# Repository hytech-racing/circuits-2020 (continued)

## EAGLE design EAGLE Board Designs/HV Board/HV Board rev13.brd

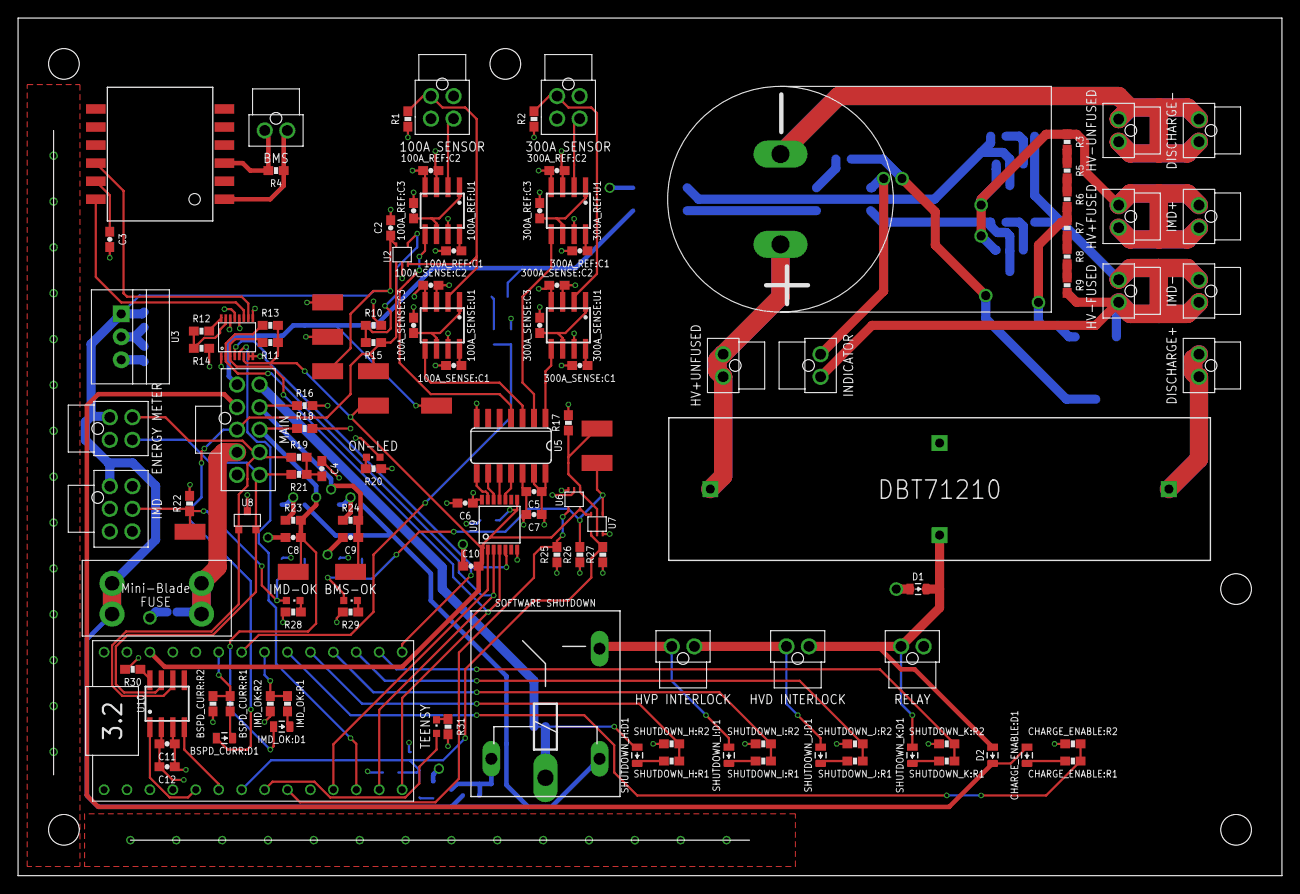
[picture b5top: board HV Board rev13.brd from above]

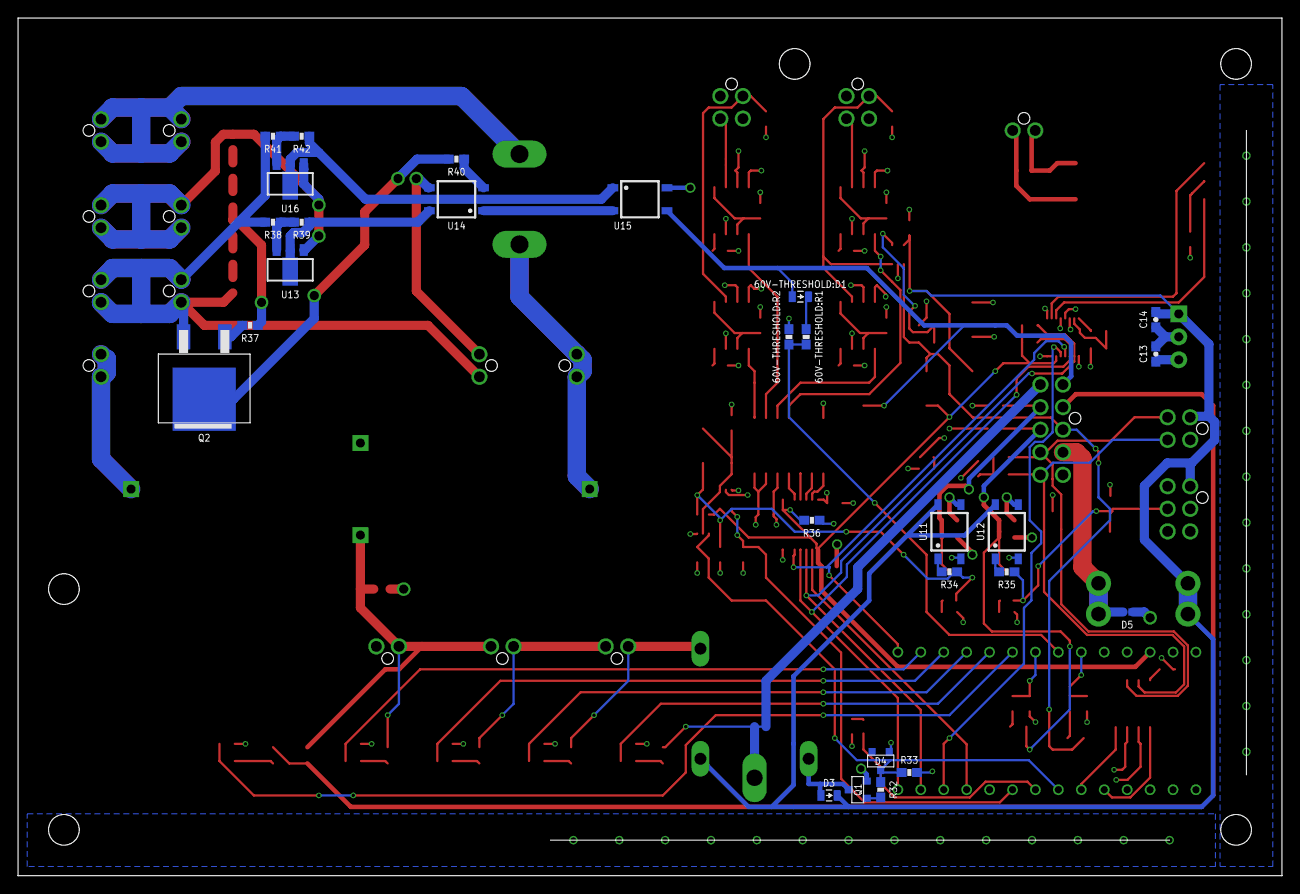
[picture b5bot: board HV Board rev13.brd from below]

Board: 4 copper layers, 140.0 x 95.0 mm, 161 parts (27 on the bottom side), 104 nets.

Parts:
60V-THRESHOLD:D1: TS4148 RYG; 0805_D
60V-THRESHOLD:R1: 12k; 0603-RES
60V-THRESHOLD:R2: 10k; 0603-RES
100A_REF:C1, 100A_SENSE:C1, 300A_REF:C1, 300A_SENSE:C1: 530pF; 0603-CAP
100A_REF:C2, 100A_REF:C3, 100A_SENSE:C2, 100A_SENSE:C3, 300A_REF:C2, 300A_REF:C3, 300A_SENSE:C2, 300A_SENSE:C3: 0.1uF; 0603-CAP
100A_REF:U1, 100A_SENSE:U1, 300A_REF:U1, 300A_SENSE:U1: MAX7480; SOIC-08
$$U$1, $$U$2: M3_MOUNTING
$$U$12: DBT71210
BMS-OK: GREEN; LED-603
BOARDFUSE: 2A; MINI-BLADE_FUSE_HOLDER
BSPD_CURR:D1: TS4148 RYG; 0805_D
BSPD_CURR:R1: 12K; 0603-RES
BSPD_CURR:R2: 43K; 0603-RES
C1: 180uF; LLS2V181MELA
C2, C5, C6, C8, C9, C10, C11: 0.1uF; 0603-CAP
C3: 27pF; 0603-CAP
C4: 4.7nF; 0603-CAP
C7, C12: 1uF; 0603-CAP
C13, C14: 10uF; 0603-CAP
CHARGE_ENABLE:D1: TS4148 RYG; 0805_D
CHARGE_ENABLE:R1: 12K; 0603-RES
CHARGE_ENABLE:R2: 43K; 0603-RES
CURRENT1: 100A SENSOR; NANO-FIT_VERTICAL-4
CURRENT2: 300A SENSOR; NANO-FIT_VERTICAL-4
D1, D2, D3: TS4148 RYG; 0805_D
D4: MMBZ5246BLT1G; SOT23
D5: TVS_DIODE; U-DFN1608-2
DISCHARGE+: DISCHARGE+; NANO-FIT_VERTICAL-2
DISCHARGE-: DISCHARGE-; NANO-FIT_VERTICAL-2
ENERGYMETER: ENERGY METER; NANO-FIT_VERTICAL-4
HV+FUSED: HV+FUSED; NANO-FIT_VERTICAL-2
HV+UNFUSED: HV+UNFUSED; NANO-FIT_VERTICAL-2
HV-FUSED: HV-FUSED; NANO-FIT_VERTICAL-2
HV-UNFUSED: HV-UNFUSED; NANO-FIT_VERTICAL-2
IMD: IMD; NANO-FIT_VERTICAL-6
IMD+: IMD+; NANO-FIT_VERTICAL-2
IMD-: IMD-; NANO-FIT_VERTICAL-2
IMD-OK: YELLOW; LED-603
IMD_OK:D1: TS4148 RYG; 0805_D
IMD_OK:R1: 12K; 0603-RES
IMD_OK:R2: 43K; 0603-RES
INDICATOR: INDICATOR; NANO-FIT_VERTICAL-2
INTERLOCK1: HVP INTERLOCK; NANO-FIT_VERTICAL-2
INTERLOCK2: HVD INTERLOCK; NANO-FIT_VERTICAL-2
ISOSPI: BMS; NANO-FIT_VERTICAL-2
MAIN: MAIN; NANO-FIT_VERTICAL-10
ON-LED: BLUE; LED-603
Q1: DMG3406L; SOT23
Q2: AOD1N60; TO-252
R1, R2, R25: 10K; 0603-RES
R3, R5, R6: 510k; 0603-RES
R4: 100; 0603-RES
R7, R8, R9: 43k; 0603-RES
R10, R12, R14, R30, R31, R40: 1k; 0603-RES
R11, R13, R39, R42: 2k; 0603-RES
R15: 1.4k; 0603-RES
R16, R17, R18, R22, R26, R27, R33, R36: 10k; 0603-RES
R19, R21: 60; 0603-RES
R20, R28, R29: 1K; 0603-RES
R23, R24: 1.6K; 0603-RES
R32, R37: 10; 0603-RES
R34: 360; 0603-RES
R35: 4.7k; 0603-RES
R38: 20k; 0603-RES
R41: 8.2k; 0603-RES
RELAY: RELAY; NANO-FIT_VERTICAL-2
SHUTDOWN_H:D1: TS4148 RYG; 0805_D
SHUTDOWN_H:R1: 12K; 0603-RES
SHUTDOWN_H:R2: 43K; 0603-RES
SHUTDOWN_I:D1: TS4148 RYG; 0805_D
SHUTDOWN_I:R1: 12K; 0603-RES
SHUTDOWN_I:R2: 43K; 0603-RES
SHUTDOWN_J:D1: TS4148 RYG; 0805_D
SHUTDOWN_J:R1: 12K; 0603-RES
SHUTDOWN_J:R2: 43K; 0603-RES
SHUTDOWN_K:D1: TS4148 RYG; 0805_D
SHUTDOWN_K:R1: 12K; 0603-RES
SHUTDOWN_K:R2: 43K; 0603-RES
SOFTWARE_SHUTDOWN: SOFTWARE SHUTDOWN; G5LE-1A4
TEENSY: RED; LED-603
TEENSY3.1: TEENSY_3.2_SIMPLE
U1: HM2102NLT
U2: OPA172; SOT323-5
U3: OKI-78SR-5; OKI-78SR
U4: LTC6820; MSOP-16
U5: MCP3204; SO14
U6: STWD100PYW83F; SOT323-5
U7: SN74LVC1G08; SOT323-5
U8: CDSOT23-T24CAN-Q; SOT23
U9: TXB0104TSSOP; TSSOP-14
U10: MCP2551; SOIC-08
U11, U12, U14, U15: CPC1002N; SOP04
U13, U16: LR8; SOT89
U$3, U$4, U$5, U$6, U$7, U$8, U$9, U$10, U$11, U$13, U$14: TEST_POINTMICRO_MINIATURE; MICRO_MINIATURE
U$15, U$16, U$17: M3_MOUNTING

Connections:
60V-THRESHOLD:INPUT_POST_DIODE: 60V-THRESHOLD:D1.C, 60V-THRESHOLD:R1.1
60V_THRESHOLD_SIGNAL: 60V-THRESHOLD:D1.A, MAIN.P$1, U15.3, U$8.P$1
60V_THRESHOLD_TEENSY: 60V-THRESHOLD:R1.2, 60V-THRESHOLD:R2.1, TEENSY3.1.A6
100A_REF: 100A_REF:U1.2, CURRENT1.P$3
100A_REF:CLK: 100A_REF:C1.1, 100A_REF:U1.8
100A_REF:COM: 100A_REF:C3.1, 100A_REF:U1.1, 100A_REF:U1.6
100A_REF_FILT: 100A_REF:U1.5, U5.4
100A_SENSE: 100A_SENSE:U1.2, CURRENT1.P$2, R1.1, U2.3
100A_SENSE:CLK: 100A_SENSE:C1.1, 100A_SENSE:U1.8
100A_SENSE:COM: 100A_SENSE:C3.1, 100A_SENSE:U1.1, 100A_SENSE:U1.6
100A_SENSE_FILT: 100A_SENSE:U1.5, U5.3
300A_REF: 300A_REF:U1.2, CURRENT2.P$3
300A_REF:CLK: 300A_REF:C1.1, 300A_REF:U1.8
300A_REF:COM: 300A_REF:C3.1, 300A_REF:U1.1, 300A_REF:U1.6
300A_REF_FILT: 300A_REF:U1.5, U5.2
300A_SENSE: 300A_SENSE:U1.2, CURRENT2.P$2, R2.1
300A_SENSE:CLK: 300A_SENSE:C1.1, 300A_SENSE:U1.8
300A_SENSE:COM: 300A_SENSE:C3.1, 300A_SENSE:U1.1, 300A_SENSE:U1.6
300A_SENSE_FILT: 300A_SENSE:U1.5, U5.1
+3V3: C10.1, R11.1, R13.1, R36.1, TEENSY3.1.3.3V, U4.6, U6.5, U7.5, U9.1, U9.8, U$7.P$1
+5V: 100A_REF:C2.1, 100A_REF:U1.4, 100A_REF:U1.7, 100A_SENSE:C2.1, 100A_SENSE:U1.4, 100A_SENSE:U1.7, 300A_REF:C2.1, 300A_REF:U1.4, 300A_REF:U1.7, 300A_SENSE:C2.1, 300A_SENSE:U1.4, 300A_SENSE:U1.7, C5.1, C6.1, C7.1, C11.2, C12.2, C13.1, CURRENT1.P$1, CURRENT2.P$1, ON-LED.A, TEENSY3.1.VIN, U3.3, U4.1, U4.7, U4.8, U4.9, U4.12, U5.13, U5.14, U9.14, U10.3, U15.4, U$4.P$1
+12V: BOARDFUSE.R1, BOARDFUSE.R2, C2.2, C14.1, D3.C, ENERGYMETER.P$1, IMD.P$1, SOFTWARE_SHUTDOWN.2, U2.5, U3.1, U11.4, U12.4, U$5.P$1
+12VIN: BOARDFUSE.L1, BOARDFUSE.L2, D5.P$2, MAIN.P$4
BMS_OK: C9.2, MAIN.P$7, R16.1, R24.2, U$14.P$1
BMS_OK_3.3V: BMS-OK.A, R26.2, R34.1, U7.4, U$10.P$1
BMS_OK_PRE_FILTER: R24.1, U11.3
BMS_STATUS: D4.3, R27.2, R32.2, R33.1, TEENSY3.1.D5, U7.1
BSPD_CURR:INPUT_POST_DIODE: BSPD_CURR:D1.C, BSPD_CURR:R1.1
BSPD_CURRENT: BSPD_CURR:D1.A, MAIN.P$3, R15.2, U2.1, U$6.P$1
BSPD_CURR_TEENSY: BSPD_CURR:R1.2, BSPD_CURR:R2.1, TEENSY3.1.A7
CANH: ENERGYMETER.P$4, MAIN.P$10, R21.2, U8.2, U10.7
CANL: ENERGYMETER.P$3, MAIN.P$9, R19.2, U8.1, U10.6
CANRX: TEENSY3.1.D4(CANRX), U10.4
CANTX: TEENSY3.1.D3(CANTX), U10.1
CHARGE_ENABLE: CHARGE_ENABLE:D1.A, D2.C, MAIN.P$2
CHARGE_ENABLE:INPUT_POST_DIODE: CHARGE_ENABLE:D1.C, CHARGE_ENABLE:R1.1
CHARGE_ENABLE_TEENSY: CHARGE_ENABLE:R1.2, CHARGE_ENABLE:R2.1, TEENSY3.1.A4
CS_ADC_5V: U5.8, U9.13
CS_ADC_TEENSY: TEENSY3.1.D9(RX2), U9.2
CS_LTC6820: TEENSY3.1.D10(TX2), U4.5
DISCHARGE+: $$U$12.CONTACT2, DISCHARGE+.P$1, DISCHARGE+.P$2
GND: 60V-THRESHOLD:R2.2, 100A_REF:C1.2, 100A_REF:C2.2, 100A_REF:C3.2, 100A_REF:U1.3, 100A_SENSE:C1.2, 100A_SENSE:C2.2, 100A_SENSE:C3.2, 100A_SENSE:U1.3, 300A_REF:C1.2, 300A_REF:C2.2, 300A_REF:C3.2, 300A_REF:U1.3, 300A_SENSE:C1.2, 300A_SENSE:C2.2, 300A_SENSE:C3.2, 300A_SENSE:U1.3, $$U$12.COIL+, BSPD_CURR:R2.2, C2.1, C3.2, C4.1, C5.2, C6.2, C7.2, C8.1, C9.1, C10.2, C11.1, C12.1, C13.2, C14.2, CHARGE_ENABLE:R2.2, CURRENT1.P$4, CURRENT2.P$4, D1.A, D4.1, D5.P$1, ENERGYMETER.P$2, IMD.P$2, IMD.P$3, IMD.P$4, IMD_OK:R2.2, MAIN.P$5, Q1.2, R1.2, R2.2, R10.2, R14.2, R16.2, R17.1, R18.2, R20.2, R22.2, R25.2, R26.1, R27.1, R28.2, R29.2, R30.1, R31.2, R33.2, R36.2, RELAY.P$2, SHUTDOWN_H:R2.2, SHUTDOWN_I:R2.2, SHUTDOWN_J:R2.2, SHUTDOWN_K:R2.2, TEENSY3.1.AGND, TEENSY3.1.GND, U2.2, U3.2, U4.13, U4.14, U5.7, U5.12, U6.2, U6.3, U7.3, U8.3, U9.7, U10.2, U11.2, U12.2, U$3.P$1
HV+FUSED: HV+FUSED.P$1, HV+FUSED.P$2, IMD+.P$1, IMD+.P$2, R3.2, U13.1, U16.1
HV+UNFUSED: $$U$12.CONTACT1, C1.P$1, HV+UNFUSED.P$1, HV+UNFUSED.P$2
HV-FUSED: HV-FUSED.P$1, HV-FUSED.P$2, IMD-.P$1, IMD-.P$2, INDICATOR.P$2, Q2.3, R9.1, R38.2, R41.2
HV-UNFUSED: C1.P$2, DISCHARGE-.P$1, DISCHARGE-.P$2, HV-UNFUSED.P$1, HV-UNFUSED.P$2
IM: U1.P$10, U4.10
IMD_OK: C8.2, IMD_OK:D1.A, MAIN.P$8, R18.1, R23.2, U$13.P$1
IMD_OK:INPUT_POST_DIODE: IMD_OK:D1.C, IMD_OK:R1.1
IMD_OK_12V: IMD.P$5, IMD-OK.A, R22.1, R35.1, U$11.P$1
IMD_OK_PRE_FILTER: R23.1, U12.3
IMD_OK_TEENSY: IMD_OK:R1.2, IMD_OK:R2.1, TEENSY3.1.A5
IP: U1.P$12, U4.11
ISOSPI-M: ISOSPI.P$2, R4.2, U1.P$3
ISOSPI-P: ISOSPI.P$1, R4.1, U1.P$1
MISO_5V: U5.10, U9.11
MISO_TEENSY: R13.2, TEENSY3.1.D12, U4.3, U9.4
MOSI_5V: U5.9, U9.12
MOSI_TEENSY: R11.2, TEENSY3.1.D11, U4.2, U9.3
unnamed: D3.A, Q1.3, SOFTWARE_SHUTDOWN.1
unnamed: ON-LED.C, R20.1
unnamed: Q2.1, R37.2
unnamed: R39.2, U13.2, U13.PAD, U14.4
unnamed: R38.1, R39.1, U13.3
unnamed: R10.1, R15.1, U2.4
unnamed: R35.2, U12.1
unnamed: IMD-OK.C, R28.1
unnamed: C4.2, R19.1, R21.1
unnamed: Q1.1, R32.1
unnamed: R34.2, U11.1
unnamed: BMS-OK.C, R29.1
unnamed: R42.2, U15.1, U16.2, U16.PAD
unnamed: R3.1, R5.1
unnamed: R5.2, R6.2
unnamed: R30.2, U10.8
unnamed: R7.1, R8.1
unnamed: R8.2, R9.2
unnamed: R31.1, TEENSY.C
unnamed: R40.1, U14.2
unnamed: R12.1, U4.16
unnamed: R12.2, R14.1, U4.15
unnamed: U14.1, U15.2
unnamed: INDICATOR.P$1, U14.3
unnamed: C3.1, U1.P$11
unnamed: R41.1, R42.1, U16.3
unnamed: R6.1, R7.2, R37.1
unnamed: Q2.2(TAB), R40.2
SCK_5V: U5.11, U9.10
SCK_TEENSY: TEENSY3.1.D13, U4.4, U9.5
SHUTDOWN_H: MAIN.P$6, SHUTDOWN_H:D1.A, SOFTWARE_SHUTDOWN.P
SHUTDOWN_H:INPUT_POST_DIODE: SHUTDOWN_H:D1.C, SHUTDOWN_H:R1.1
SHUTDOWN_H_TEENSY: SHUTDOWN_H:R1.2, SHUTDOWN_H:R2.1, TEENSY3.1.A3
SHUTDOWN_I: INTERLOCK1.P$1, SHUTDOWN_I:D1.A, SOFTWARE_SHUTDOWN.S
SHUTDOWN_I:INPUT_POST_DIODE: SHUTDOWN_I:D1.C, SHUTDOWN_I:R1.1
SHUTDOWN_I_TEENSY: SHUTDOWN_I:R1.2, SHUTDOWN_I:R2.1, TEENSY3.1.A2
SHUTDOWN_J: INTERLOCK1.P$2, INTERLOCK2.P$1, SHUTDOWN_J:D1.A
SHUTDOWN_J:INPUT_POST_DIODE: SHUTDOWN_J:D1.C, SHUTDOWN_J:R1.1
SHUTDOWN_J_TEENSY: SHUTDOWN_J:R1.2, SHUTDOWN_J:R2.1, TEENSY3.1.A1
SHUTDOWN_K: $$U$12.COIL-, D1.C, D2.A, INTERLOCK2.P$2, RELAY.P$1, SHUTDOWN_K:D1.A
SHUTDOWN_K:INPUT_POST_DIODE: SHUTDOWN_K:D1.C, SHUTDOWN_K:R1.1
SHUTDOWN_K_TEENSY: SHUTDOWN_K:R1.2, SHUTDOWN_K:R2.1, TEENSY3.1.A0
TEENSY_STATUS: TEENSY.A, TEENSY3.1.D6
WATCHDOG_INPUT: R25.1, TEENSY3.1.D7(RX3), U6.4
WATCHDOG_OK: R17.2, U6.1, U7.2, U$9.P$1

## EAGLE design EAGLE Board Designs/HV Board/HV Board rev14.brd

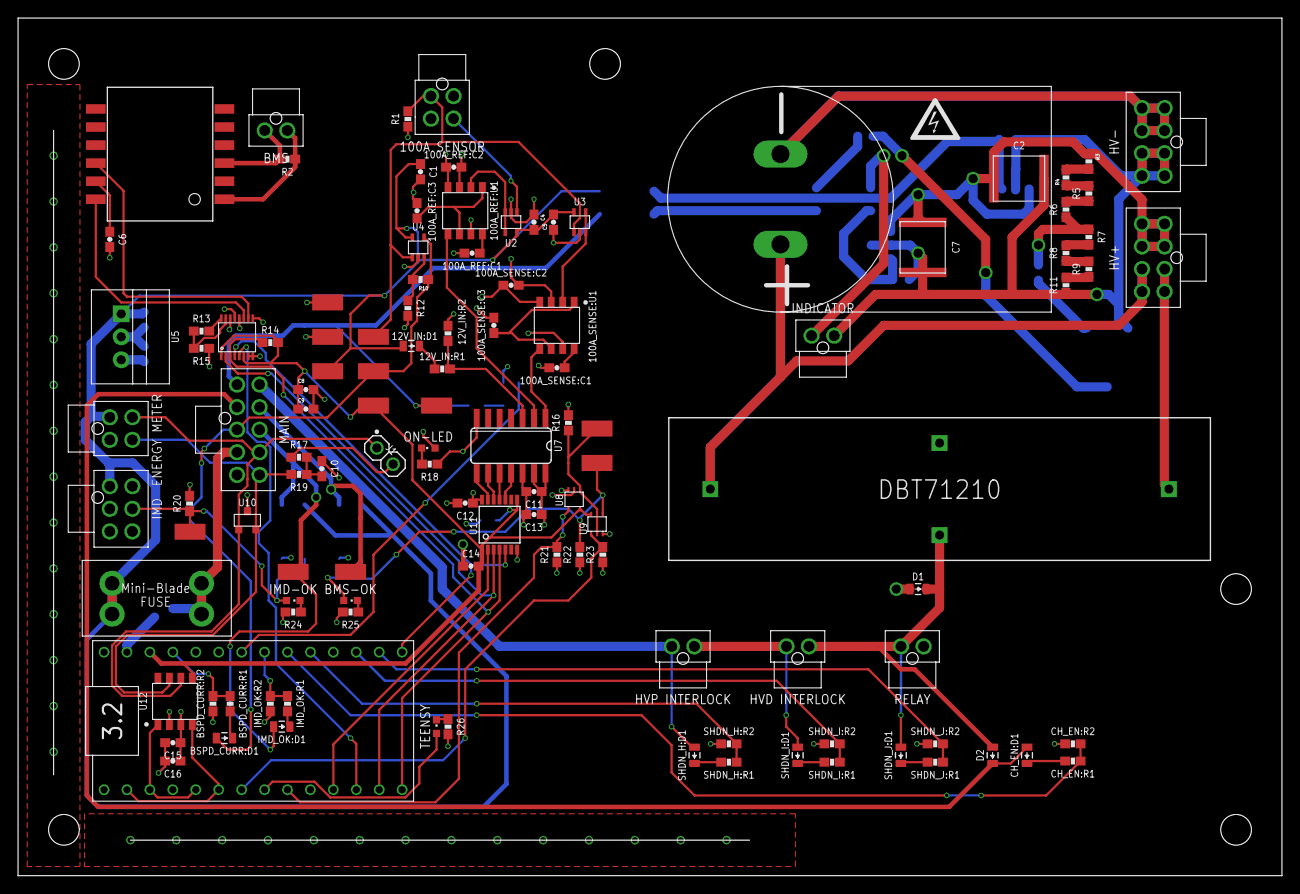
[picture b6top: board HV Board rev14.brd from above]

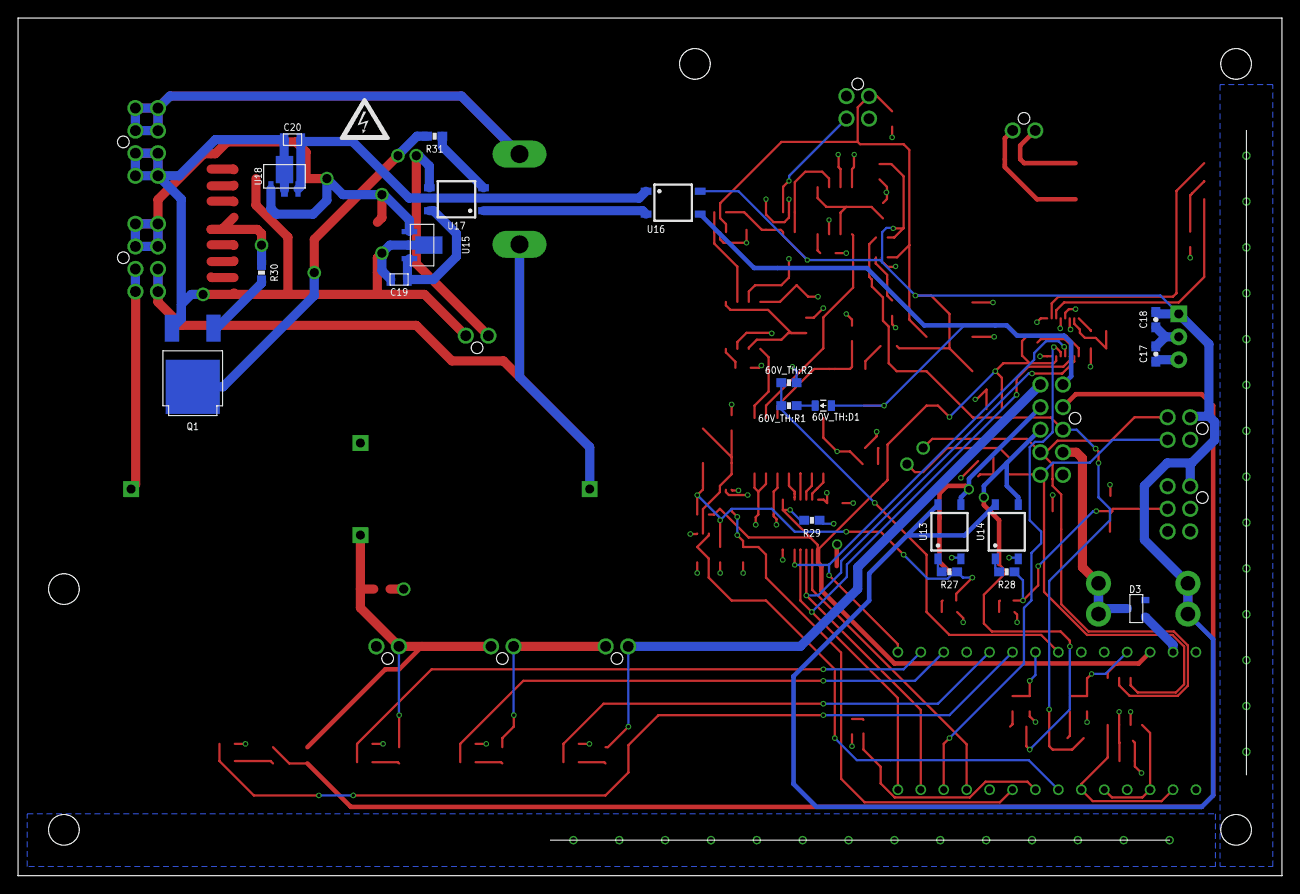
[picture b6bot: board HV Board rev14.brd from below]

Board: 4 copper layers, 140.0 x 95.0 mm, 143 parts (21 on the bottom side), 93 nets.

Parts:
12V_IN:D1, 60V_TH:D1: TS4148 RYG; 0805_D
12V_IN:R1, 60V_TH:R1: 12K; 0603-RES@1
12V_IN:R2, 60V_TH:R2: 43K; 0603-RES@1
100A_REF:C1, 100A_SENSE:C1: 680pF; 0603-CAP@1
100A_REF:C2, 100A_REF:C3, 100A_SENSE:C2, 100A_SENSE:C3: 0.1uF; 0603-CAP@1
100A_REF:U1, 100A_SENSE:U1: MAX7480; SOIC-08@2
$$$$U$3: DBT71210
$$U$1, $$U$2: M3_MOUNTING
$$U$3, $$U$12: TEST_POINTMICRO_MINIATURE; MICRO_MINIATURE
BMS-OK: GREEN; LED-603
BOARDFUSE: 2A; MINI-BLADE_FUSE_HOLDER
BSPD_CURR:D1: TS4148 RYG; 0805_D
BSPD_CURR:R1: 12K; 0603-RES@1
BSPD_CURR:R2: 43K; 0603-RES@1
C1, C4, C5, C9, C11, C12, C14, C15: 0.1uF; 0603-CAP@1
C2, C7: CAPACITOR_2220_630V_1UF; 2220-CAP
C3: 180uF; LLS2V181MELA
C6: 27pF; 0603-CAP@1
C8, C13, C16: 1uF; 0603-CAP@1
C10: 4.7nF; 0603-CAP@1
C17, C18: 10uF; 0603-CAP@1
C19, C20: CAPACITOR_0805_25V_22UF; 0805-CAP
CH_EN:D1: TS4148 RYG; 0805_D
CH_EN:R1: 12K; 0603-RES@1
CH_EN:R2: 43K; 0603-RES@1
CURRENT1: 100A SENSOR; NANO-FIT_VERTICAL-4
D1, D2: TS4148 RYG; 0805_D
D3: TVS_15V; SOT-23
ENERGYMETER: ENERGY METER; NANO-FIT_VERTICAL-4
HV+: CONNECTOR-8_NF_T_V_NATURAL; MOLEX_NANOFIT_PTH_08
HV-: CONNECTOR-8_NF_T_V_BLACK; MOLEX_NANOFIT_PTH_08
IMD: IMD; NANO-FIT_VERTICAL-6
IMD-OK: YELLOW; LED-603
IMD_OK:D1: TS4148 RYG; 0805_D
IMD_OK:R1: 12K; 0603-RES@1
IMD_OK:R2: 43K; 0603-RES@1
INDICATOR: INDICATOR; NANO-FIT_VERTICAL-2
INTERLOCK1: HVP INTERLOCK; NANO-FIT_VERTICAL-2
INTERLOCK2: HVD INTERLOCK; NANO-FIT_VERTICAL-2
ISOSPI: BMS; NANO-FIT_VERTICAL-2
J1: JUMPER.1; 1X02
MAIN: MAIN; NANO-FIT_VERTICAL-10
ON-LED: BLUE; LED-603
Q1: TRANSISTOR_N_MOS_2-7K1S_TK6P65W; DPAK(2-7K1S)
R1, R21: 10K; 0603-RES@1
R2: 100; 0603-RES@1
R3, R4, R5, R6: 162k; 0603-RES@1
R7, R8, R9, R11, R16, R20, R22, R23, R29: 10k; 0603-RES@1
R10: 1.4k; 0603-RES@1
R12, R13, R15, R26: 1k; 0603-RES@1
R14: 2k; 0603-RES@1
R17, R19: 60; 0603-RES@1
R18, R24, R25: 1K; 0603-RES@1
R27: 360; 0603-RES@1
R28: 4.7k; 0603-RES@1
R30: 10; 0603-RES@1
R31: 5k; 0603-RES@1
RELAY: RELAY; NANO-FIT_VERTICAL-2
SHDN_H:D1: TS4148 RYG; 0805_D
SHDN_H:R1: 12K; 0603-RES@1
SHDN_H:R2: 43K; 0603-RES@1
SHDN_I:D1: TS4148 RYG; 0805_D
SHDN_I:R1: 12K; 0603-RES@1
SHDN_I:R2: 43K; 0603-RES@1
SHDN_J:D1: TS4148 RYG; 0805_D
SHDN_J:R1: 12K; 0603-RES@1
SHDN_J:R2: 43K; 0603-RES@1
TEENSY: RED; LED-603
TEENSY3.1: TEENSY_3.2_SIMPLE
U1: HM2102NLT
U2, U3, U4: OPAMP_1_CHANNEL_OPA991; SC-70-5
U5: OKI-78SR-5; OKI-78SR@1
U6: LTC6820; MSOP-16
U7: MCP3204; SO14
U8: STWD100PYW83F; SOT323-5
U9: SN74LVC1G08; SOT323-5
U10: CDSOT23-T24CAN-Q; SOT23
U11: TXB0104TSSOP; TSSOP-14
U12: CAN_TRANSCIEVER_TCAN1051HQV-Q1; SOIC-08
U13, U14, U16, U17: CPC1002N; SOP04
U15, U18: VOLTAGE_REGULATOR_SOT89_12V; SOT89
U$3, U$4, U$5, U$6, U$7, U$8, U$9, U$10, U$11, U$13: TEST_POINTMICRO_MINIATURE; MICRO_MINIATURE
U$14, U$15, U$16: M3_MOUNTING
U$17, U$19: HV_0.50"

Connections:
12V_IN:INPUT_POST_DIODE: 12V_IN:D1.C, 12V_IN:R1.1
60V_TH:INPUT_POST_DIODE: 60V_TH:D1.C, 60V_TH:R1.1
60V_THRESHOLD_SIGNAL: 60V_TH:D1.A, MAIN.P$1, U16.3, U$8.P$1
60V_THRESHOLD_TEENSY: 60V_TH:R1.2, 60V_TH:R2.1, TEENSY3.1.A6
100A_REF: CURRENT1.P$3, U2.1
100A_REF:CLK: 100A_REF:C1.1, 100A_REF:U1.8
100A_REF:COM: 100A_REF:C3.1, 100A_REF:U1.1, 100A_REF:U1.6
100A_REF_BUFF: 100A_REF:U1.2, U2.3, U2.4
100A_REF_FILT: 100A_REF:U1.5, U7.2
100A_SENSE: CURRENT1.P$2, R1.1, U3.1, U4.1, U$4.P$1
100A_SENSE:CLK: 100A_SENSE:C1.1, 100A_SENSE:U1.8
100A_SENSE:COM: 100A_SENSE:C3.1, 100A_SENSE:U1.1, 100A_SENSE:U1.6
100A_SENSE_BUFF: 100A_SENSE:U1.2, U3.3, U3.4
100A_SENSE_FILT: 100A_SENSE:U1.5, U7.1
+3V3: C8.1, C9.1, C14.1, R14.1, R29.1, TEENSY3.1.3.3V, U6.1, U6.6, U8.5, U9.5, U11.1, U11.8, U12.5, U$7.P$1
+5V: 100A_REF:C2.1, 100A_REF:U1.4, 100A_REF:U1.7, 100A_SENSE:C2.1, 100A_SENSE:U1.4, 100A_SENSE:U1.7, $$U$3.P$1, C11.1, C12.1, C13.1, C15.2, C16.2, C17.1, CURRENT1.P$1, ON-LED.A, TEENSY3.1.VIN, U5.3, U6.7, U6.8, U6.9, U6.12, U7.13, U7.14, U11.14, U12.3
+12V: 12V_IN:D1.A, BOARDFUSE.R1, BOARDFUSE.R2, C1.2, C4.2, C5.2, C18.1, ENERGYMETER.P$1, IMD.P$1, U2.5, U3.5, U4.5, U5.1, U13.4, U14.4, U16.4, U$5.P$1
+12VIN: BOARDFUSE.L1, BOARDFUSE.L2, D3.3, MAIN.P$4
+12V_SCALED_3.3V: 12V_IN:R1.2, 12V_IN:R2.1, U7.3
BMS_OK: MAIN.P$7, U13.3, U$13.P$1
BMS_OK_3.3V: BMS-OK.A, R22.2, R27.1, U9.4, U$10.P$1
BMS_STATUS: R23.2, TEENSY3.1.D5, U9.1
BSPD_CURR:INPUT_POST_DIODE: BSPD_CURR:D1.C, BSPD_CURR:R1.1
BSPD_CURRENT: BSPD_CURR:D1.A, MAIN.P$3, R10.1, U4.4, U$6.P$1
BSPD_CURR_TEENSY: BSPD_CURR:R1.2, BSPD_CURR:R2.1, TEENSY3.1.A9
CANH: ENERGYMETER.P$4, MAIN.P$10, R19.2, U10.2, U12.7
CANL: ENERGYMETER.P$3, J1.1, MAIN.P$9, U10.1, U12.6
CANRX: TEENSY3.1.D0(RX1), TEENSY3.1.D4(CANRX), U12.4
CANTX: TEENSY3.1.D1(TX1), TEENSY3.1.D3(CANTX), U12.1
CHARGE_ENABLE: CH_EN:D1.A, D2.C, MAIN.P$2
CHARGE_ENABLE_TEENSY: CH_EN:R1.2, CH_EN:R2.1, TEENSY3.1.A4
CH_EN:INPUT_POST_DIODE: CH_EN:D1.C, CH_EN:R1.1
CS_ADC_5V: U7.8, U11.13
CS_ADC_TEENSY: TEENSY3.1.D9(RX2), U11.2
CS_LTC6820: TEENSY3.1.D10(TX2), U6.5
DISCHARGE+: $$$$U$3.CONTACT2, HV+.1, HV+.2
GND: 12V_IN:R2.2, 60V_TH:R2.2, 100A_REF:C1.2, 100A_REF:C2.2, 100A_REF:C3.2, 100A_REF:U1.3, 100A_SENSE:C1.2, 100A_SENSE:C2.2, 100A_SENSE:C3.2, 100A_SENSE:U1.3, $$$$U$3.COIL+, BSPD_CURR:R2.2, C1.1, C4.1, C5.1, C6.2, C8.2, C9.2, C10.1, C11.2, C12.2, C13.2, C14.2, C15.1, C16.1, C17.2, C18.2, CH_EN:R2.2, CURRENT1.P$4, D1.A, D3.1, ENERGYMETER.P$2, IMD.P$2, IMD.P$3, IMD.P$4, IMD_OK:R2.2, MAIN.P$5, R1.2, R12.2, R15.2, R16.1, R18.2, R20.2, R21.2, R22.1, R23.1, R24.2, R25.2, R26.2, R29.2, RELAY.P$2, SHDN_H:R2.2, SHDN_I:R2.2, SHDN_J:R2.2, TEENSY3.1.AGND, TEENSY3.1.GND, U2.2, U3.2, U4.2, U5.2, U6.13, U6.14, U7.7, U7.12, U8.2, U8.3, U9.3, U10.3, U11.7, U12.2, U13.2, U14.2, U$3.P$1
HV+FUSED: C2.1, C7.1, HV+.3, HV+.4, HV+.7, HV+.8, R3.1, U15.1, U18.1
HV+UNFUSED: $$$$U$3.CONTACT1, C3.P$1, HV+.5, HV+.6
HV-FUSED: C2.2, C7.2, C19.2, C20.2, HV-.1, HV-.2, HV-.5, HV-.6, INDICATOR.P$2, Q1.3, R11.2, U15.2, U15.2@2, U18.2, U18.2@2
HV-UNFUSED: C3.P$2, HV-.3, HV-.4, HV-.7, HV-.8
IM: U1.P$10, U6.10
IMD_OK: $$U$12.P$1, IMD_OK:D1.A, MAIN.P$8, U14.3
IMD_OK:INPUT_POST_DIODE: IMD_OK:D1.C, IMD_OK:R1.1
IMD_OK_12V: IMD.P$5, IMD-OK.A, R20.1, R28.1, U$11.P$1
IMD_OK_TEENSY: IMD_OK:R1.2, IMD_OK:R2.1, TEENSY3.1.A5
IP: U1.P$12, U6.11
ISOSPI-M: ISOSPI.P$2, R2.2, U1.P$3
ISOSPI-P: ISOSPI.P$1, R2.1, U1.P$1
MISO_5V: U7.10, U11.11
MISO_TEENSY: R14.2, TEENSY3.1.D12, U6.3, U11.4
MOSI_5V: U7.9, U11.12
MOSI_TEENSY: TEENSY3.1.D11, U6.2, U11.3
unnamed: ON-LED.C, R18.1
unnamed: Q1.1, R30.2
unnamed: C19.1, U15.3, U17.4
unnamed: R9.1, R11.1
unnamed: R28.2, U14.1
unnamed: IMD-OK.C, R24.1
unnamed: R8.2, R9.2
unnamed: C10.2, R17.1, R19.1
unnamed: R7.1, R8.1
unnamed: R10.2, R12.1, U4.3
unnamed: R27.2, U13.1
unnamed: BMS-OK.C, R25.1
unnamed: C20.1, U16.1, U18.3
unnamed: R6.1, R7.2, R30.1
unnamed: R5.2, R6.2
unnamed: R4.1, R5.1
unnamed: R3.2, R4.2
unnamed: J1.2, R17.2
unnamed: R26.1, TEENSY.C
unnamed: R31.1, U17.2
unnamed: R13.1, U6.16
unnamed: R13.2, R15.1, U6.15
unnamed: U16.2, U17.1
unnamed: INDICATOR.P$1, U17.3
unnamed: C6.1, U1.P$11
unnamed: Q1.2, R31.2
SCK_5V: U7.11, U11.10
SCK_TEENSY: TEENSY3.1.D13, U6.4, U11.5
SHDN_H:INPUT_POST_DIODE: SHDN_H:D1.C, SHDN_H:R1.1
SHDN_I:INPUT_POST_DIODE: SHDN_I:D1.C, SHDN_I:R1.1
SHDN_J:INPUT_POST_DIODE: SHDN_J:D1.C, SHDN_J:R1.1
SHUTDOWN_H: INTERLOCK1.P$1, MAIN.P$6, SHDN_H:D1.A
SHUTDOWN_H_TEENSY: SHDN_H:R1.2, SHDN_H:R2.1, TEENSY3.1.A3
SHUTDOWN_I: INTERLOCK1.P$2, INTERLOCK2.P$1, SHDN_I:D1.A
SHUTDOWN_I_TEENSY: SHDN_I:R1.2, SHDN_I:R2.1, TEENSY3.1.A1
SHUTDOWN_J: $$$$U$3.COIL-, D1.C, D2.A, INTERLOCK2.P$2, RELAY.P$1, SHDN_J:D1.A
SHUTDOWN_J_TEENSY: SHDN_J:R1.2, SHDN_J:R2.1, TEENSY3.1.A0
TEENSY_STATUS: TEENSY.A, TEENSY3.1.D6
WATCHDOG_INPUT: R21.1, TEENSY3.1.D7(RX3), U8.4
WATCHDOG_OK: R16.2, U8.1, U9.2, U$9.P$1

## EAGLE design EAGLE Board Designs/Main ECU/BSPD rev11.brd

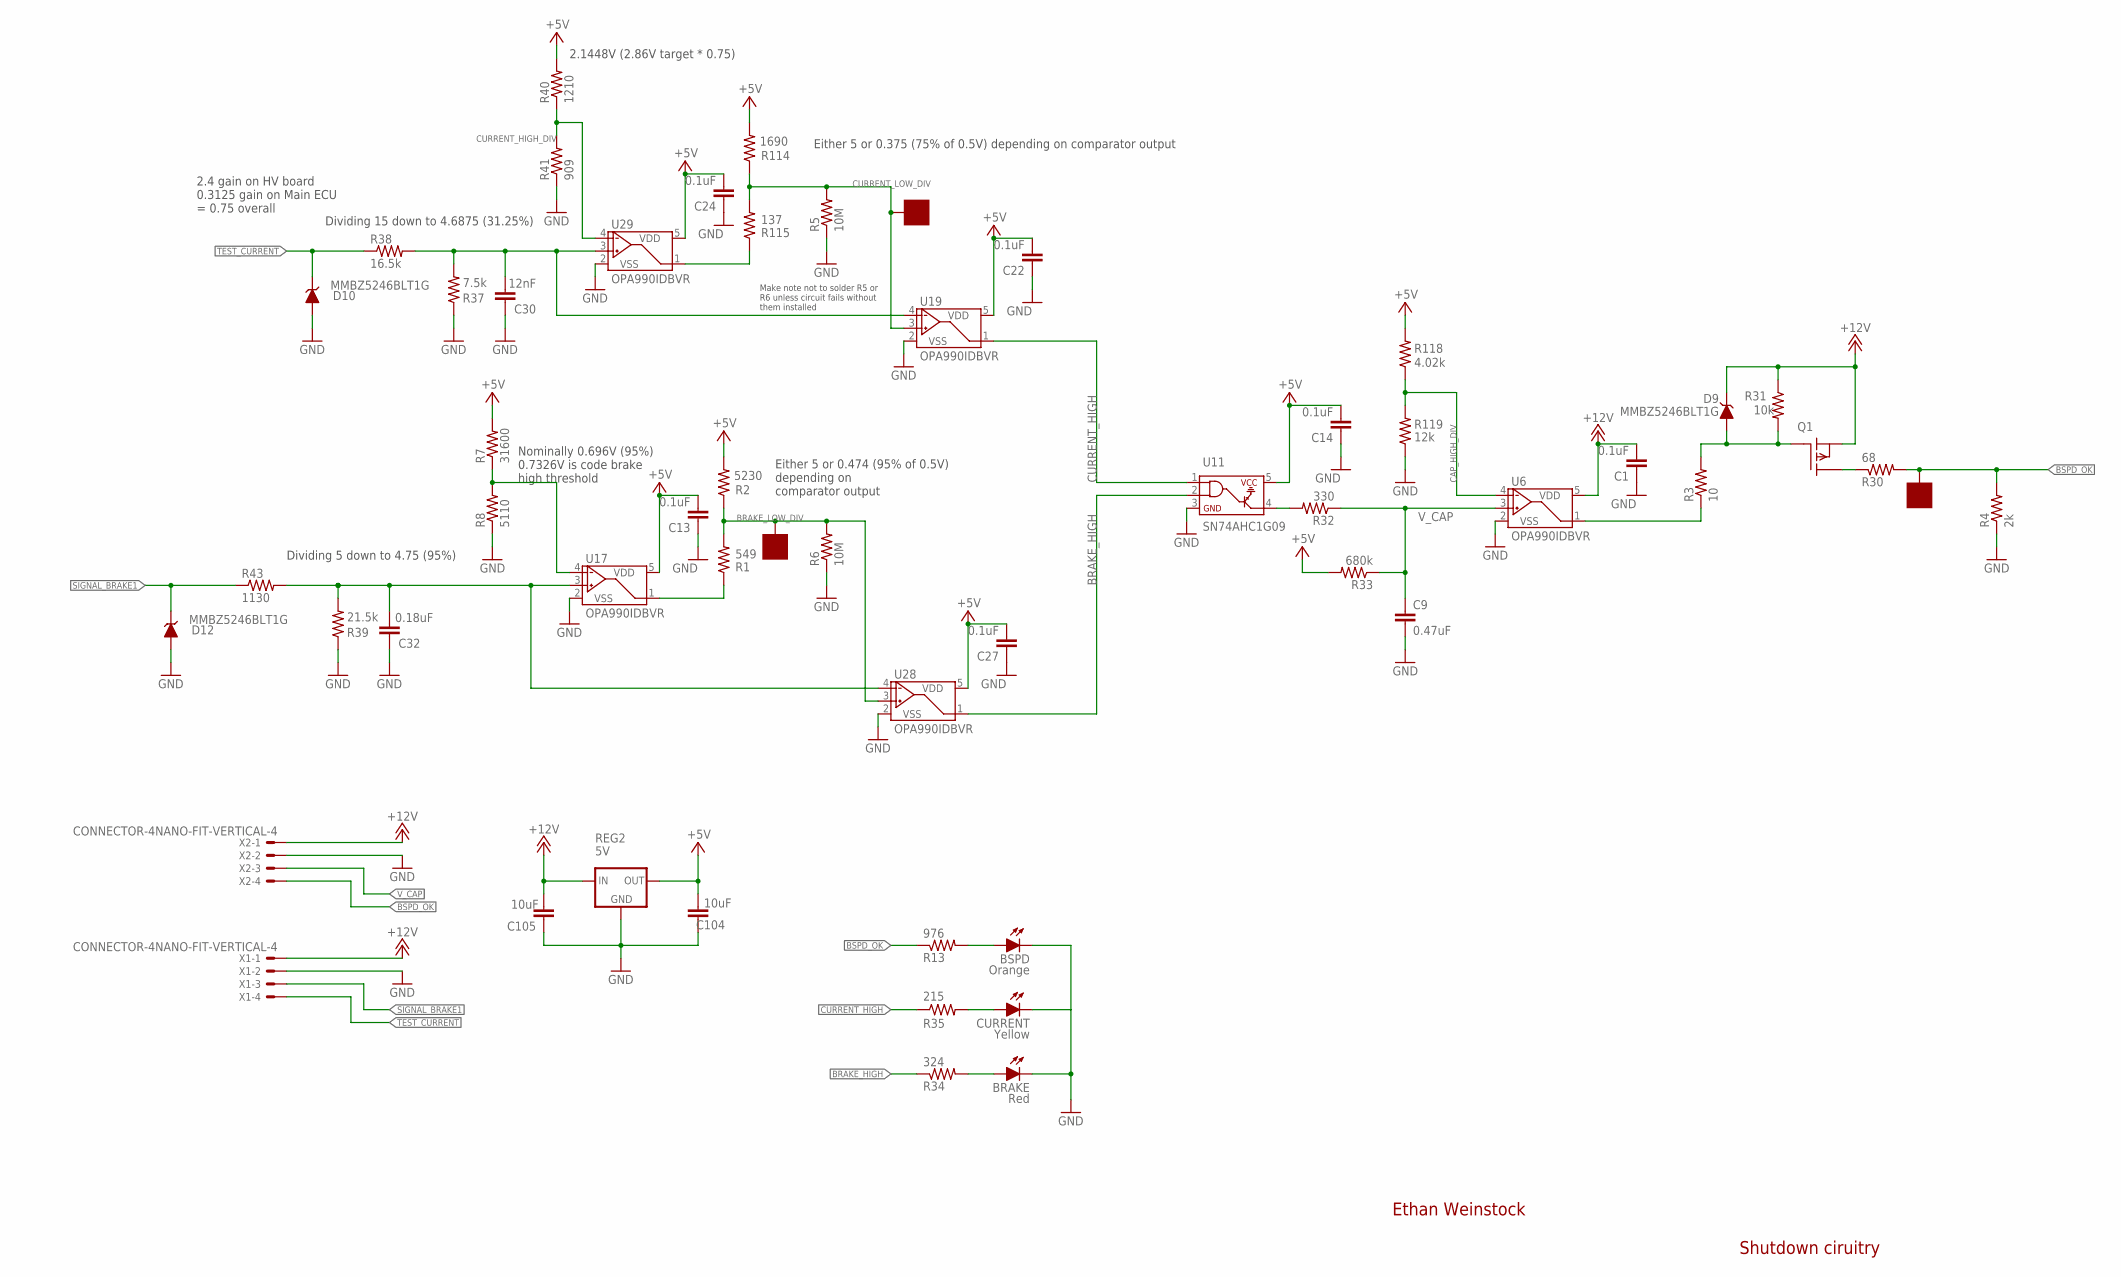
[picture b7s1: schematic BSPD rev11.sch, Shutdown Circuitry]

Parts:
BRAKE: Red; LED-805
BSPD: Orange; LED-805
C1, C13, C14, C22, C24, C27: 0.1uF; 0603-CAP
C9: 0.47uF; 0603-CAP
C30: 12nF; 0603-CAP
C32: 0.18uF; 0603-CAP
C104, C105: 10uF; 0603-CAP
CURRENT: Yellow; LED-805
D9, D10, D12: MMBZ5246BLT1G; SOT23
Q1: P-CHANNEL_MOSFET_DMP3099L-7; SOT23
R1: 549; 0603-RES
R2: 5230; 0603-RES
R3: 10; 0603-RES
R4: 2k; 0603-RES
R5, R6: 10M; 0603-RES
R7: 31600; 0603-RES
R8: 5110; 0603-RES
R13: 976; 0603-RES
R30: 68; 0603-RES
R31: 10k; 0603-RES
R32: 330; 0603-RES
R33: 680k; 0603-RES
R34: 324; 0603-RES
R35: 215; 0603-RES
R37: 7.5k; 0603-RES
R38: 16.5k; 0603-RES
R39: 21.5k; 0603-RES
R40: 1210; 0603-RES
R41: 909; 0603-RES
R43: 1130; 0603-RES
R114: 1690; 0603-RES
R115: 137; 0603-RES
R118: 4.02k; 0603-RES
R119: 12k; 0603-RES
REG2: 5V; OKI-78SR
U6, U17, U19, U28, U29: OPA990IDBVR; SOT-23-5
U11: SN74AHC1G09; SOT-23-5
U$1, U$2, U$3: SOLDER_PAD; SOLDER_PAD_XSMALL
X1, X2: CONNECTOR-4NANO-FIT-VERTICAL-4; NANO-FIT_VERTICAL-4

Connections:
+5V: C13.2, C14.2, C22.2, C24.2, C27.2, C104.2, R2.2, R7.2, R33.2, R40.2, R114.2, R118.2, REG2.3 (OUT), U11.5, U17.5 (VDD), U19.5 (VDD), U28.5 (VDD), U29.5 (VDD)
+12V: C1.2, C105.2, D9.3 (C), Q1.2 (S), R31.1, REG2.1 (IN), U6.5 (VDD), X1.P$1, X2.P$1
BRAKE_HIGH: R34.1, U11.2, U28.1 (VOUT)
BRAKE_LOW_DIV: R1.2, R2.1, R6.2, U28.3 (VIN+), U$1.P$1
BSPD_OK: R4.2, R13.1, R30.2, U$3.P$1, X2.P$4
CAP_HIGH_DIV: R118.1, R119.2, U6.4 (VIN-)
CURRENT_HIGH: R35.1, U11.1, U19.1 (VOUT)
CURRENT_HIGH_DIV: R40.1, R41.2, U29.4 (VIN-)
CURRENT_LOW_DIV: R5.2, R114.1, R115.2, U19.3 (VIN+), U$2.P$1
GND: C1.1, C9.2, C13.1, C14.1, C22.1, C24.1, C27.1, C30.1, C32.1, C104.1, C105.1, D10.1 (A), D12.1 (A), R4.1, R5.1, R6.1, R8.1, R37.1, R39.1, R41.1, R119.1, REG2.2 (GND), U6.2 (VSS), U11.3, U17.2 (VSS), U19.2 (VSS), U28.2 (VSS), U29.2 (VSS), X1.P$2, X2.P$2
GND1: BRAKE.C, BSPD.C, CURRENT.C
unnamed: Q1.3 (D), R30.1
unnamed: R1.1, U17.1 (VOUT)
unnamed: R3.1, U6.1 (VOUT)
unnamed: C32.2, R39.2, R43.2, U17.3 (VIN+), U28.4 (VIN-)
unnamed: R7.1, R8.2, U17.4 (VIN-)
unnamed: R115.1, U29.1 (VOUT)
unnamed: CURRENT.A, R35.2
unnamed: BRAKE.A, R34.2
unnamed: C30.2, R37.2, R38.2, U19.4 (VIN-), U29.3 (VIN+)
unnamed: R32.2, U11.4
unnamed: BSPD.A, R13.2
unnamed: D9.1 (A), Q1.1 (G), R3.2, R31.2
SIGNAL_BRAKE1: D12.3 (C), R43.1, X1.P$3
TEST_CURRENT: D10.3 (C), R38.1, X1.P$4
V_CAP: C9.1, R32.1, R33.1, U6.3 (VIN+), X2.P$3

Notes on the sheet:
Ethan Weinstock
Shutdown ciruitry
Dividing 15 down to 4.6875 (31.25%)
Either 5 or 0.375 (75% of 0.5V) depending on comparator output
2.1448V (2.86V target * 0.75)
Either 5 or 0.474 (95% of 0.5V) depending on comparator output
Nominally 0.696V (95%) 0.7326V is code brake high threshold
Dividing 5 down to 4.75 (95%)
2.4 gain on HV board 0.3125 gain on Main ECU = 0.75 overall
Make note not to solder R5 or R6 unless circuit fails without them installed

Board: 2 copper layers, 55 parts (0 on the bottom side), 26 nets, no tracks yet.
